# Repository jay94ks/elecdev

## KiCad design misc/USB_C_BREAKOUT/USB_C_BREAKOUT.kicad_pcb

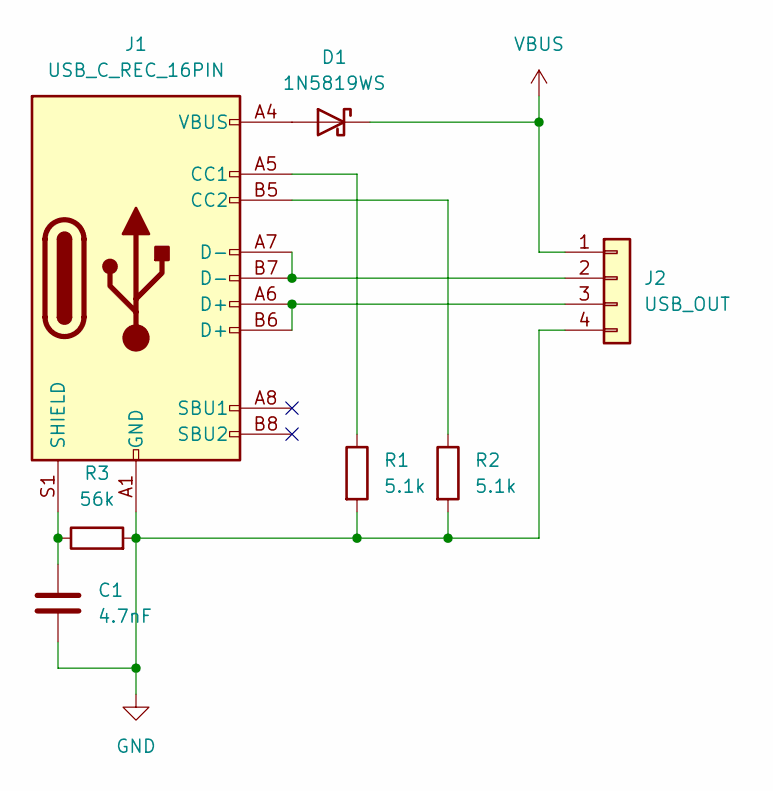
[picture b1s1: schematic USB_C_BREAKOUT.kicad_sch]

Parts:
C1: 4.7nF; C_0603_1608Metric
D1: 1N5819WS; D_SOD-323_HandSoldering
J1: USB_C_REC_16PIN; USB_C_Receptacle_Palconn_UTC16-G
J2: USB_OUT; PinHeader_1x04_P2.54mm_Horizontal
R1, R2: 5.1k; R_0603_1608Metric
R3: 56k; R_0603_1608Metric

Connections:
GND: C1.2, J1.A1 (GND), J1.A12 (GND), J1.B1 (GND), J1.B12 (GND), J2.4, R1.2, R2.2, R3.2
unnamed: D1.2 (A), J1.A4 (VBUS), J1.A9 (VBUS), J1.B4 (VBUS), J1.B9 (VBUS)
unnamed: J1.A5 (CC1), R1.1
unnamed: J1.B5 (CC2), R2.1
unnamed: C1.1, J1.S1 (SHIELD), R3.1
unnamed: J1.A7 (D-), J1.B7 (D-), J2.2
unnamed: J1.A6 (D+), J1.B6 (D+), J2.3
VBUS: D1.1 (K), J2.1

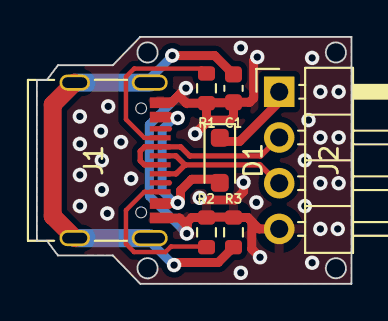
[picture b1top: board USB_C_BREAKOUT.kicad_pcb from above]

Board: 2 copper layers, 17.5 x 13.7 mm, 7 parts (0 on the bottom side), 8 nets.

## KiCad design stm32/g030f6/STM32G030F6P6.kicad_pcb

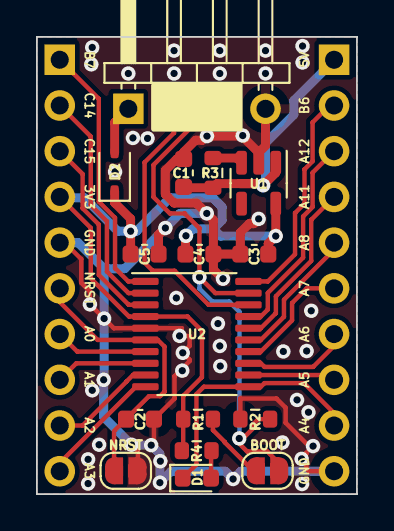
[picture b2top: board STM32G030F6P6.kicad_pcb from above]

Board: 2 copper layers, 17.8 x 25.4 mm, 18 parts (0 on the bottom side), 25 nets.

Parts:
C1, C3, C5: 10uF; C_0603_1608Metric
C2, C4: 100nF; C_0603_1608Metric
D1: BLUE; LED_0603_1608Metric
D2: 1N5819WS; D_SOD-323
J1: STLINK; PinHeader_1x04_P2.54mm_Horizontal
J2: LEFT; PinHeader_1x10_P2.54mm_Vertical
J3: RIGHT; PinHeader_1x10_P2.54mm_Vertical
JP1: RESET; SolderJumper-2_P1.3mm_Open_RoundedPad1.0x1.5mm
JP2: BOOT0; SolderJumper-2_P1.3mm_Open_RoundedPad1.0x1.5mm
R1: 330; R_0603_1608Metric
R2, R4: 10k; R_0603_1608Metric
R3: 100k; R_0603_1608Metric
U1: XC6220B331MR; SOT-23-5
U2: STM32G030F6Px; TSSOP-20_4.4x6.5mm_P0.65mm

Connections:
+3.3V: C3.2, C4.1, C5.1, D2.1 (K), J2.4, R1.1, R4.1, U1.5 (VOUT), U2.4 (VDD)
+5V: C1.2, J3.1, R3.2, U1.1 (VIN)
GND: C1.1, C2.1, C3.1, C4.2, C5.2, J1.4, J2.5, J3.10, JP1.1 (A), R2.2, U1.2 (GND), U2.5 (VSS)
NRST: C2.2, J2.6, JP1.2 (B), U2.6 (NRST)
unnamed: D1.2 (A), R4.2
unnamed: D2.2 (A), J1.1
unnamed: JP2.1 (A), R1.2
unnamed: R3.1, U1.3 (CE)
PA0: J2.7, U2.7 (PA0)
PA1: J2.8, U2.8 (PA1)
PA2: J2.9, U2.9 (PA2)
PA3: J2.10, U2.10 (PA3)
PA4: D1.1 (K), J3.9, U2.11 (PA4)
PA5: J3.8, U2.12 (PA5)
PA6: J3.7, U2.13 (PA6)
PA7: J3.6, U2.14 (PA7)
PA8: J3.5, U2.15 (PB0/PB1/PB2/PA8)
PA11: J3.4, U2.16 (PA11/PA9)
PA12: J3.3, U2.17 (PA12/PA10)
PB6: J3.2, U2.20 (PB3/PB4/PB5/PB6)
PB7: J2.1, U2.1 (PB7/PB8)
PC14: J2.2, U2.2 (PC14/PB9)
PC15: J2.3, U2.3 (PC15)
SWCLK/BOOT0: J1.3, JP2.2 (B), R2.1, U2.19 (PA14/PA15)
SWDIO: J1.2, U2.18 (PA13)
